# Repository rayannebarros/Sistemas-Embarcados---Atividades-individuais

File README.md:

# Sistemas-Embarcados---Atividades-individuais
Atividades individuais realizadas na disciplina de Sistemas Embarcados, no período 2021.2

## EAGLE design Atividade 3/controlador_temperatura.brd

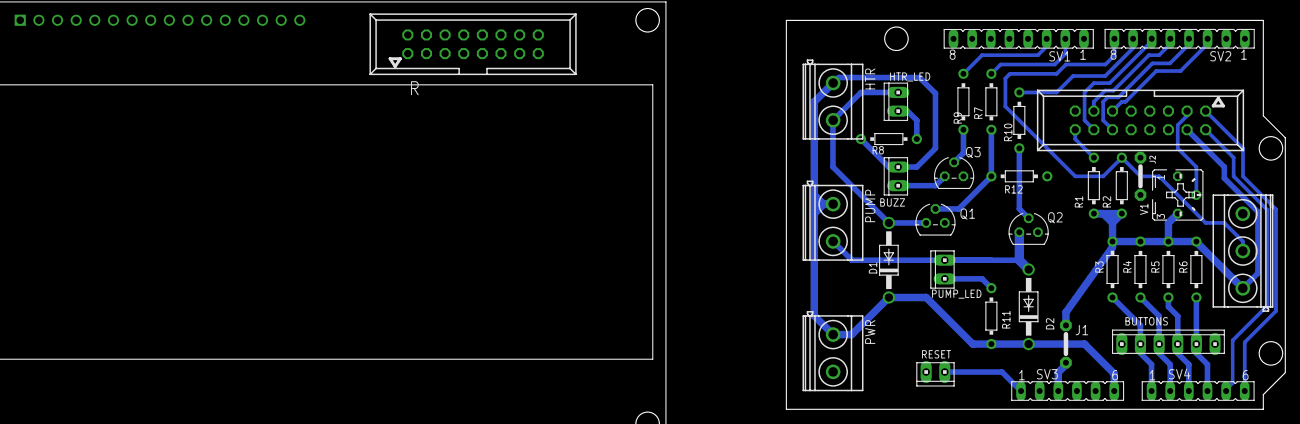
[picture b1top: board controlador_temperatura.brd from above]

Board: 2 copper layers, 68.0 x 53.0 mm, 36 parts (0 on the bottom side), 38 nets.

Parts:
A: LCD_A; 057-016-1
BUTTONS: 10X06MTA
BUZZ: 10X02MTA
D1, D2: 1N4007; DO41-10
DS18B20: MKDSN1,5/3-5,08
HTR: MKDSN1,5/2-5,08
HTR_LED: 10X02MTA
J1, J2: J5MM; 05
LCD: LCD-HD447804-HOLES20X4-4HOLES; LCD-20X4-4HOLES
PUMP: MKDSN1,5/2-5,08
PUMP_LED: 10X02MTA
PWR: MKDSN1,5/2-5,08
Q1, Q2, Q3: BC337; TO92
R: LCD_B; 057-016-1
R1: 220; RS1/8
R2: 4.7k; RS1/8
R3, R4, R5, R6, R12: 10k; RS1/8
R7, R8, R9, R10, R11: 470; RS1/8
RESET: 10X02MTA
SV1, SV2: FE08
SV3, SV4: FE06
V1: 10K; B25P

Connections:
+5V: A.4, DS18B20.1, J1.1, J1.2, R1.2, R2.2, R3.2, R4.2, R5.2, R6.2, SV3.3, V1.E
A0: BUTTONS.5, R3.1, SV4.1
A1: BUTTONS.4, R4.1, SV4.2
A2: BUTTONS.3, R5.1, SV4.3
A3: BUTTONS.2, R6.1, SV4.4
A4: A.2, SV4.5
A5: A.1, SV4.6
D2: A.11, SV2.3
D3: A.12, SV2.4
D4: A.13, SV2.5
D5: A.14, SV2.6
D6: R10.1, SV2.7
D7: DS18B20.2, R2.1, SV2.8
D9: R7.2, SV1.2
D10: R9.1, SV1.3
GND: A.7, A.8, A.9, A.10, BUTTONS.1, BUTTONS.6, DS18B20.3, J2.1, J2.2, PWR.2, Q1.1, Q2.1, Q3.1, R12.1, RESET.1, SV1.7, SV3.4, SV3.5, V1.A
HTR: D1.A, HTR.2, HTR_LED.1, Q1.3
unnamed: Q1.2, R7.1, R12.2
unnamed: Q3.2, R9.2
unnamed: HTR_LED.2, R8.1
unnamed: Q2.2, R10.2
unnamed: A.3, V1.S
unnamed: PUMP_LED.2, R11.2
unnamed: BUZZ.2, Q3.3
unnamed: A.16, R1.1
unnamed: LCD.P$6, R.1
unnamed: LCD.P$1, LCD.P$5, LCD.P$7, LCD.P$8, LCD.P$9, LCD.P$10, LCD.P$16, R.7, R.8, R.9, R.10
unnamed: LCD.P$3, R.3
unnamed: LCD.P$15, R.16
unnamed: LCD.P$2, R.4
unnamed: LCD.P$4, R.2
unnamed: LCD.P$11, R.11
unnamed: LCD.P$12, R.12
unnamed: LCD.P$13, R.13
unnamed: LCD.P$14, R.14
PUMP: D2.A, PUMP.2, PUMP_LED.1, Q2.3
RST: RESET.2, SV3.1
VIN: BUZZ.1, D1.C, D2.C, HTR.1, PUMP.1, PWR.1, R8.2, R11.1, SV3.6

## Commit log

2021-12-02 Add files via upload
    Atividades 02 - GPIO e Timer (ATmega328)
2021-12-05 Create atividades
    Pasta de atividades realizadas durante o período na disciplina
2021-12-06 Create atividade_0x
2021-12-06 Rename atividades/atividade_0x to atividades/atividade_03/resposta.pdf
2021-12-06 Create atividade_03
2021-12-06 Create test
2021-12-06 Create atividade_02
2021-12-06 Commit attividade02
